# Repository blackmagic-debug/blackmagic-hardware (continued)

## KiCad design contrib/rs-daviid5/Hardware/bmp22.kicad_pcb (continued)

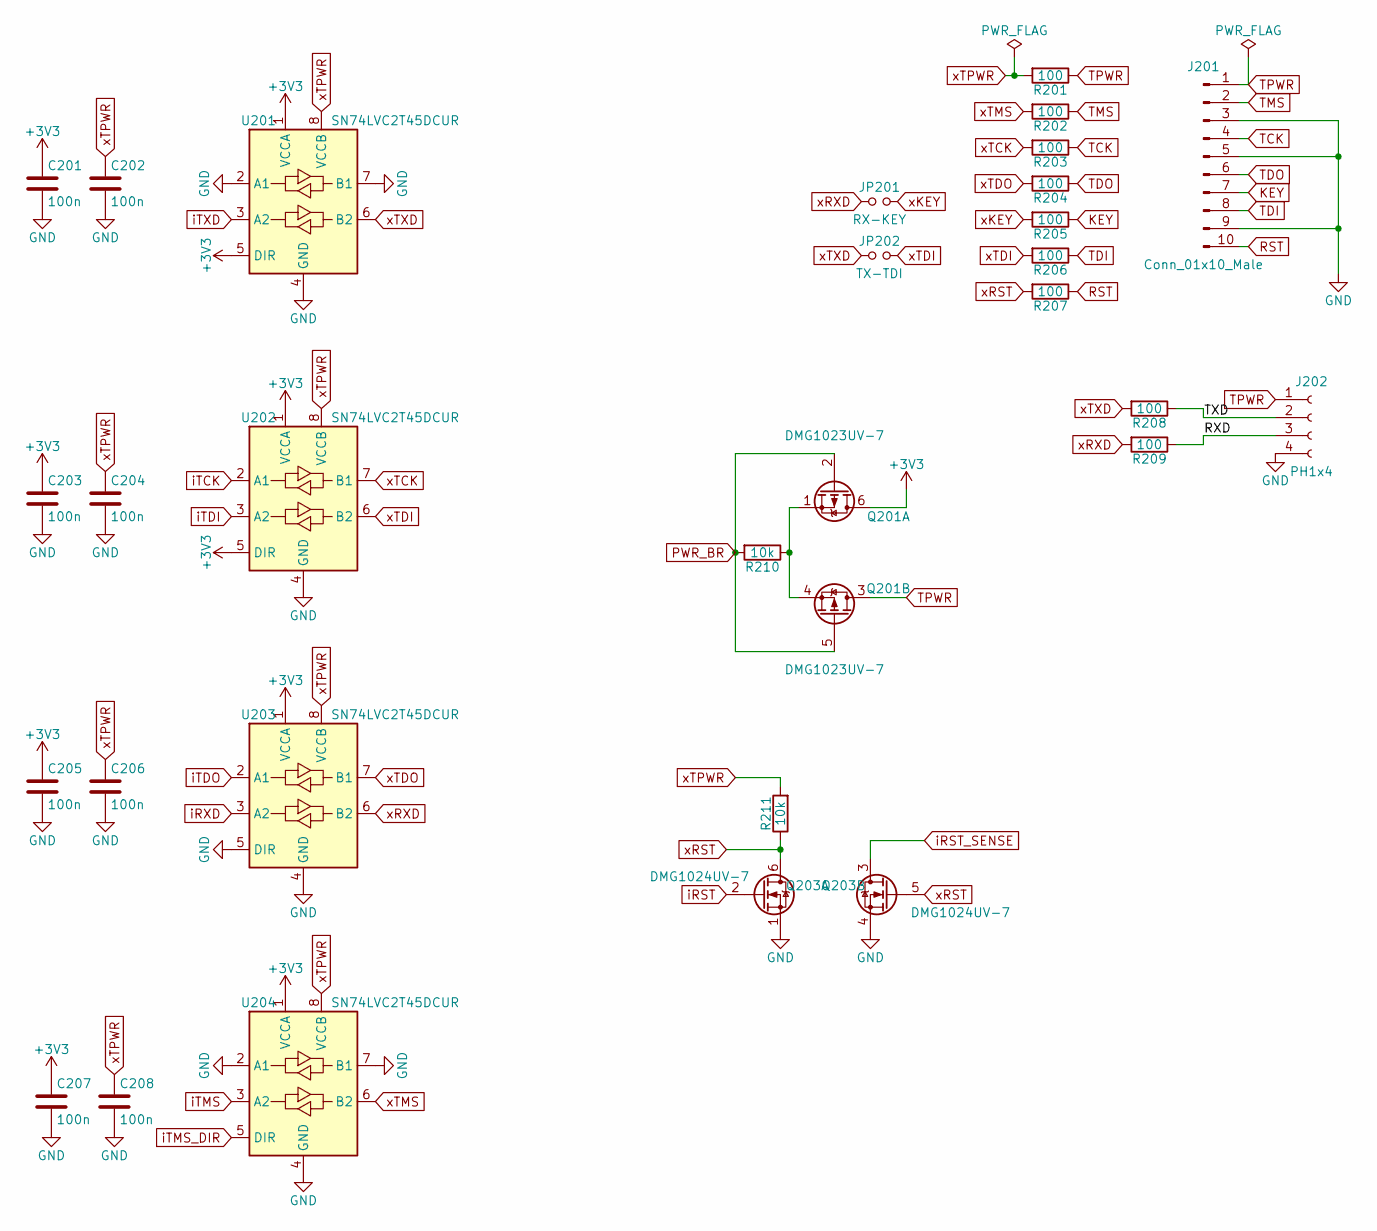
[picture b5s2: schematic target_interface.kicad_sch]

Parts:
C201, C202, C203, C204, C205, C206, C207, C208: 100n; C_0402_1005Metric; LCSC Number Part C14663
J201: Conn_01x10_Male; PinHeader_2x05_P1.27mm_Vertical_SMD; LCSC Number Part C150517
J202: PH1x4; JST_PH_S4B-PH-SM4-TB_1x04-1MP_P2.00mm_Horizontal; LCSC Number Part C265102
JP201: RX-KEY; R_0402_1005Metric; LCSC Number Part C60485
JP202: TX-TDI; R_0402_1005Metric; LCSC Number Part C60485
Q201: DMG1023UV-7; LCSC Number Part C212298
Q203: DMG1024UV-7; DMG1023UV-7; LCSC Number Part C212298
R201, R202, R203, R204, R205, R206, R207, R208, R209: 100; R_0402_1005Metric; LCSC Number Part C25076
R210, R211: 10k; R_0402_1005Metric; LCSC Number Part C25744
U201, U202, U203, U204: SN74LVC2T45DCUR; VSSOP-8_2.3x2mm_P0.5mm; LCSC Number Part C15741

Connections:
+3V3: C201.1, C203.1, C205.1, C207.1, Q201.6 (D), U201.1 (VCCA), U201.5 (DIR), U202.1 (VCCA), U202.5 (DIR), U203.1 (VCCA), U204.1 (VCCA); also elsewhere on the board
/Sheet5F21D67E/RXD: J202.3, R209.1
/Sheet5F21D67E/TXD: J202.2, R208.1
GND: C201.2, C202.2, C203.2, C204.2, C205.2, C206.2, C207.2, C208.2, J201.3, J201.5, J201.9, J202.4, Q203.1 (S), Q203.4 (S), U201.2 (A1), U201.4 (GND), U201.7 (B1), U202.4 (GND), U203.4 (GND), U203.5 (DIR), U204.2 (A1), U204.4 (GND), U204.7 (B1); also elsewhere on the board
KEY: J201.7, R205.1
unnamed: Q201.1 (S), Q201.4 (S), R210.1
PWR_BR: Q201.2 (G), Q201.5 (G), R210.2; also elsewhere on the board
RST: J201.10, R207.1
TCK: J201.4, R203.1
TDI: J201.8, R206.1
TDO: J201.6, R204.1
TMS: J201.2, R202.1
TPWR: J201.1, J202.1, Q201.3 (D), R201.1; also elsewhere on the board
iRST: Q203.2 (G); also elsewhere on the board
iRST_SENSE: Q203.3 (D); also elsewhere on the board
iRXD: U203.3 (A2); also elsewhere on the board
iTCK: U202.2 (A1); also elsewhere on the board
iTDI: U202.3 (A2); also elsewhere on the board
iTDO: U203.2 (A1); also elsewhere on the board
iTMS: U204.3 (A2); also elsewhere on the board
iTMS_DIR: U204.5 (DIR); also elsewhere on the board
iTXD: U201.3 (A2); also elsewhere on the board
xKEY: JP201.2, R205.2
xRST: Q203.5 (G), Q203.6 (D), R207.2, R211.1
xRXD: JP201.1, R209.2, U203.6 (B2)
xTCK: R203.2, U202.7 (B1)
xTDI: JP202.2, R206.2, U202.6 (B2)
xTDO: R204.2, U203.7 (B1)
xTMS: R202.2, U204.6 (B2)
xTPWR: C202.1, C204.1, C206.1, C208.1, R201.2, R211.2, U201.8 (VCCB), U202.8 (VCCB), U203.8 (VCCB), U204.8 (VCCB)
xTXD: JP202.1, R208.2, U201.6 (B2)

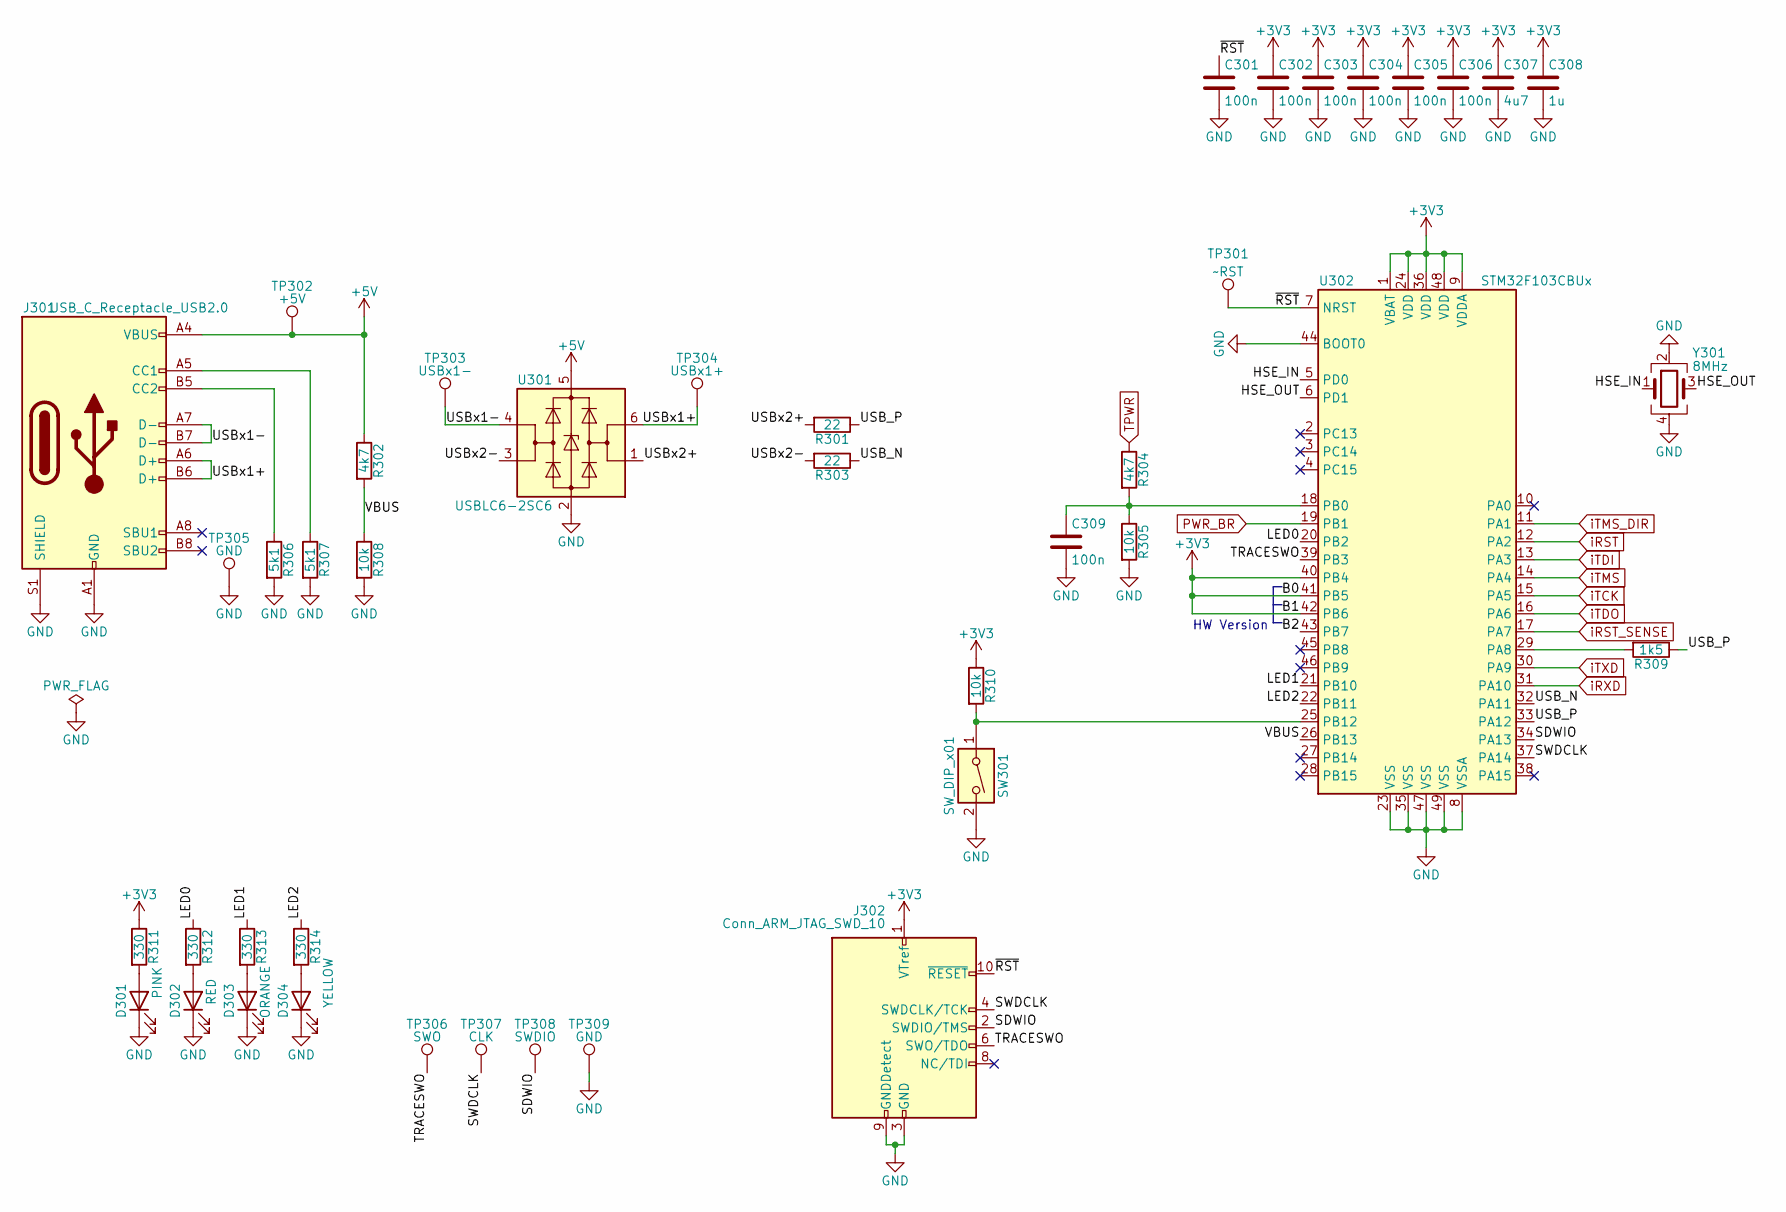
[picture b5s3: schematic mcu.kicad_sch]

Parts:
C301, C302, C303, C304, C305, C306, C309: 100n; C_0402_1005Metric; LCSC Number Part C14663
C307: 4u7; C_0603_1608Metric; LCSC Number Part C19666
C308: 1u; C_0603_1608Metric; LCSC Number Part C15849
D301: PINK; LED_1206_3216Metric; LCSC Number Part C268284
D302: RED; LED_0603_1608Metric; LCSC Number Part C375444
D303: ORANGE; LED_0603_1608Metric; LCSC Number Part C146215
D304: YELLOW; LED_0603_1608Metric; LCSC Number Part C89811
J301: USB_C_Receptacle_USB2.0; USB_C_Receptacle_Palconn_UTC16-G; LCSC Number Part C2760486
J302: Conn_ARM_JTAG_SWD_10; Tag-Connect_TC2050-IDC-NL_2x05_P1.27mm_Vertical
R301, R303: 22; R_0402_1005Metric; LCSC Number Part C25092
R302, R304: 4k7; R_0402_1005Metric; LCSC Number Part C25900
R305, R308, R310: 10k; R_0402_1005Metric; LCSC Number Part C25744
R306, R307: 5k1; R_0402_1005Metric; LCSC Number Part C25905
R309: 1k5; R_0402_1005Metric; LCSC Number Part C25867
R311, R312, R313, R314: 330; R_0402_1005Metric; LCSC Number Part C25104
SW301: SW_DIP_x01; SW_SPST_PTS810; LCSC Number Part C116501
TP301: ~RST; TestPoint_Pad_D1.5mm
TP302: +5V; TestPoint_Pad_D1.5mm
TP303: USBx1-; TestPoint_Pad_D1.5mm
TP304: USBx1+; TestPoint_Pad_D1.5mm
TP305, TP309: GND; TestPoint_Pad_D1.5mm
TP306: SWO; TestPoint_Pad_D1.5mm
TP307: CLK; TestPoint_Pad_D1.5mm
TP308: SWDIO; TestPoint_Pad_D1.5mm
U301: USBLC6-2SC6; SOT-23-6; LCSC Number Part C2827654
U302: STM32F103CBUx; TQFP48; LCSC Number Part C8304
Y301: 8MHz; Crystal_SMD_3225-4Pin_3.2x2.5mm; LCSC Number Part C435184

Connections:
+3V3: C302.1, C303.1, C304.1, C305.1, C306.1, C307.1, C308.1, J302.1 (VTref), R310.1, R311.1, U302.1 (VBAT), U302.9 (VDDA), U302.24 (VDD), U302.36 (VDD), U302.40 (PB4), U302.41 (PB5), U302.42 (PB6), U302.48 (VDD); also elsewhere on the board
+5V: J301.A4 (VBUS), J301.A9 (VBUS), J301.B4 (VBUS), J301.B9 (VBUS), R302.1, TP302.1, U301.5 (VBUS); also elsewhere on the board
/Sheet5F25207C/B2: U302.43 (PB7)
/Sheet5F25207C/HSE_IN: U302.5 (PD0), Y301.1
/Sheet5F25207C/HSE_OUT: U302.6 (PD1), Y301.3
/Sheet5F25207C/LED0: R312.1, U302.20 (PB2)
/Sheet5F25207C/LED1: R313.1, U302.21 (PB10)
/Sheet5F25207C/LED2: R314.1, U302.22 (PB11)
/Sheet5F25207C/SDWIO: J302.2 (SWDIO/TMS), TP308.1, U302.34 (PA13)
/Sheet5F25207C/SWDCLK: J302.4 (SWDCLK/TCK), TP307.1, U302.37 (PA14)
/Sheet5F25207C/TRACESWO: J302.6 (SWO/TDO), TP306.1, U302.39 (PB3)
/Sheet5F25207C/USB_N: R303.1, U302.32 (PA11)
/Sheet5F25207C/USB_P: R301.1, R309.1, U302.33 (PA12)
/Sheet5F25207C/USBx1+: J301.A6 (D+), J301.B6 (D+), TP304.1, U301.6 (I/O1)
/Sheet5F25207C/USBx1-: J301.A7 (D-), J301.B7 (D-), TP303.1, U301.4 (I/O2)
/Sheet5F25207C/USBx2+: R301.2, U301.1 (I/O1)
/Sheet5F25207C/USBx2-: R303.2, U301.3 (I/O2)
/Sheet5F25207C/VBUS: R302.2, R308.1, U302.26 (PB13)
/Sheet5F25207C/~RST: C301.1, J302.10 (~RESET), TP301.1, U302.7 (NRST)
GND: C301.2, C302.2, C303.2, C304.2, C305.2, C306.2, C307.2, C308.2, C309.2, D301.1 (K), D302.1 (K), D303.1 (K), D304.1 (K), J301.A1 (GND), J301.A12 (GND), J301.B1 (GND), J301.B12 (GND), J301.S1 (SHIELD), J302.3 (GND), J302.5 (GND), J302.9 (GNDDetect), R305.2, R306.2, R307.2, R308.2, SW301.2, TP305.1, TP309.1, U301.2 (GND), U302.8 (VSSA), U302.23 (VSS), U302.35 (VSS), U302.44 (BOOT0), U302.47 (VSS), U302.49 (VSS), Y301.2, Y301.4; also elsewhere on the board
unnamed: C309.1, R304.2, R305.1, U302.18 (PB0)
unnamed: D301.2 (A), R311.2
unnamed: D302.2 (A), R312.2
unnamed: D303.2 (A), R313.2
unnamed: D304.2 (A), R314.2
unnamed: J301.A5 (CC1), R307.1
unnamed: J301.B5 (CC2), R306.1
unnamed: R309.2, U302.29 (PA8)
unnamed: R310.2, SW301.1, U302.25 (PB12)
PWR_BR: U302.19 (PB1); also elsewhere on the board
TPWR: R304.1; also elsewhere on the board
iRST: U302.12 (PA2); also elsewhere on the board
iRST_SENSE: U302.17 (PA7); also elsewhere on the board
iRXD: U302.31 (PA10); also elsewhere on the board
iTCK: U302.15 (PA5); also elsewhere on the board
iTDI: U302.13 (PA3); also elsewhere on the board
iTDO: U302.16 (PA6); also elsewhere on the board
iTMS: U302.14 (PA4); also elsewhere on the board
iTMS_DIR: U302.11 (PA1); also elsewhere on the board
iTXD: U302.30 (PA9); also elsewhere on the board

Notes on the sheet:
HW Version

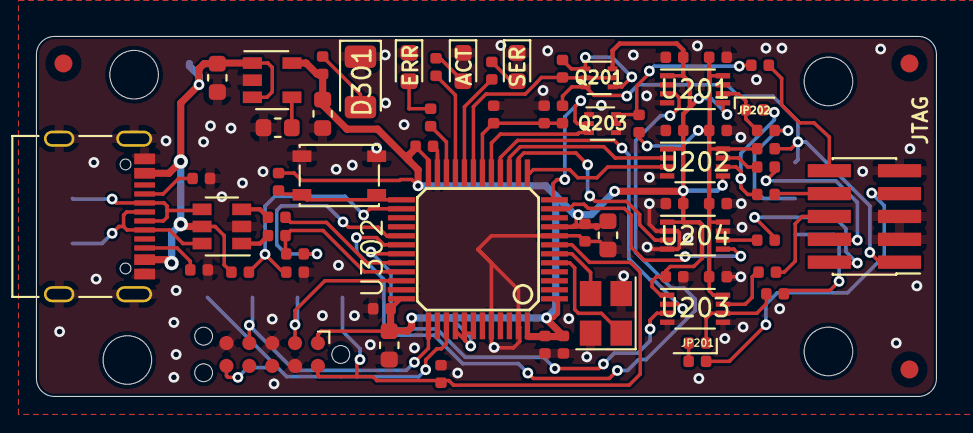
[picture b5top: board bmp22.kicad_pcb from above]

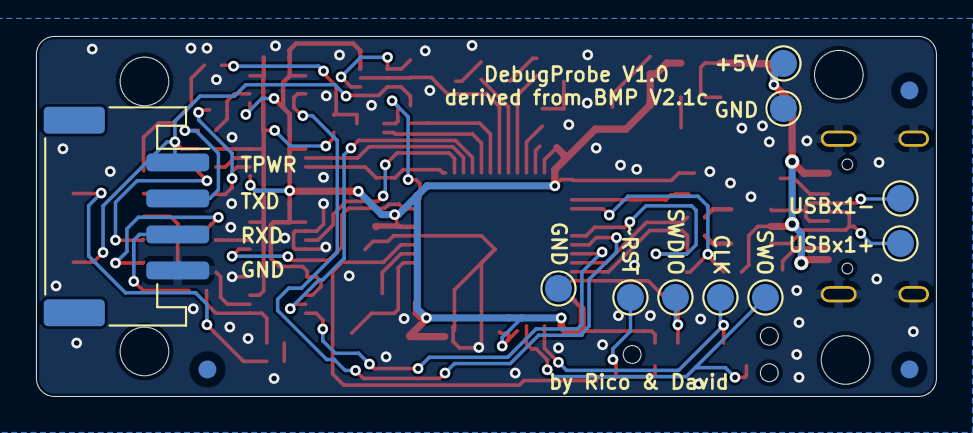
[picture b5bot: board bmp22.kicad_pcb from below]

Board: 2 copper layers, 50.0 x 20.0 mm, 85 parts (13 on the bottom side), 58 nets.

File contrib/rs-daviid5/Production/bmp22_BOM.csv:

"Source:","C:\Users\Sergio\Documents\EOS\bmp22\bmp22.kicad_sch"
"Date:","06/09/2022 16:51:32"
"Tool:","Eeschema (6.0.7)"
"Generator:","C:\Program Files\KiCad\6.0\bin\scripting\plugins/bom_csv_grouped_by_value.py"
"Component Count:","65"

"Individual Components:"

"Item","Qty","Reference(s)","Value","LibPart","Footprint","Datasheet","LCSC Number Part","Supplierlink"
"","","C101","1u","Device:C","Capacitor_SMD:C_0603_1608Metric","~","C15849",""
"","","C102","10n","Device:C","Capacitor_SMD:C_0603_1608Metric","~","C57112",""
"","","C103","1u","Device:C","Capacitor_SMD:C_0603_1608Metric","~","C15849",""
"","","C201","100n","Device:C","Capacitor_SMD:C_0402_1005Metric","~","C14663",""
"","","C202","100n","Device:C","Capacitor_SMD:C_0402_1005Metric","~","C14663",""
"","","C203","100n","Device:C","Capacitor_SMD:C_0402_1005Metric","~","C14663",""
"","","C204","100n","Device:C","Capacitor_SMD:C_0402_1005Metric","~","C14663",""
"","","C205","100n","Device:C","Capacitor_SMD:C_0402_1005Metric","~","C14663",""
"","","C206","100n","Device:C","Capacitor_SMD:C_0402_1005Metric","~","C14663",""
"","","C207","100n","Device:C","Capacitor_SMD:C_0402_1005Metric","~","C14663",""
"","","C208","100n","Device:C","Capacitor_SMD:C_0402_1005Metric","~","C14663",""
"","","C301","100n","Device:C","Capacitor_SMD:C_0402_1005Metric","~","C14663",""
"","","C302","100n","Device:C","Capacitor_SMD:C_0402_1005Metric","~","C14663",""
"","","C303","100n","Device:C","Capacitor_SMD:C_0402_1005Metric","~","C14663",""
"","","C304","100n","Device:C","Capacitor_SMD:C_0402_1005Metric","~","C14663",""
"","","C305","100n","Device:C","Capacitor_SMD:C_0402_1005Metric","~","C14663",""
"","","C306","100n","Device:C","Capacitor_SMD:C_0402_1005Metric","~","C14663",""
"","","C307","4u7","Device:C","Capacitor_SMD:C_0603_1608Metric","~","C19666",""
"","","C308","1u","Device:C","Capacitor_SMD:C_0603_1608Metric","~","C15849",""
"","","C309","100n","Device:C","Capacitor_SMD:C_0402_1005Metric","~","C14663",""
"","","D301","PINK","Device:LED","LED_SMD:LED_1206_3216Metric","~","C268284",""
"","","D302","RED","Device:LED","LED_SMD:LED_0603_1608Metric","~","C375444",""
"","","D303","ORANGE","Device:LED","LED_SMD:LED_0603_1608Metric","~","C146215",""
"","","D304","YELLOW","Device:LED","LED_SMD:LED_0603_1608Metric","~","C89811",""
"","","J201","Conn_01x10_Male","Connector:Conn_01x10_Male","Connector_PinHeader_1.27mm:PinHeader_2x05_P1.27mm_Vertical_SMD","~","C150517",""
"","","J202","PH1x4","Connector:Conn_01x04_Female","Connector_JST:JST_PH_S4B-PH-SM4-TB_1x04-1MP_P2.00mm_Horizontal","~","C265102",""
"","","J301","USB_C_Receptacle_USB2.0","bmp22-rescue:USB_C_Receptacle_USB2.0-Connector","Connector_USB:USB_C_Receptacle_Palconn_UTC16-G","https://www.usb.org/sites/default/files/documents/usb_type-c.zip","C2760486",""
"","","JP201","RX-KEY","bmp22-rescue:Jumper_NO_Small-Device","Resistor_SMD:R_0402_1005Metric","","C60485",""
"","","JP202","TX-TDI","bmp22-rescue:Jumper_NO_Small-Device","Resistor_SMD:R_0402_1005Metric","","C60485",""
"","","Q201","DMG1023UV-7","bmp22-rescue:Q_DUAL_PMOS_S1G1D2S2G2D1-Device","EOS:DMG1023UV-7","","C212298",""
"","","Q203","DMG1024UV-7","bmp22-rescue:Q_DUAL_NMOS_S1G1D2S2G2D1-Device","EOS:DMG1023UV-7","","C212298",""
"","","R201","100","Device:R","Resistor_SMD:R_0402_1005Metric","~","C25076",""
"","","R202","100","Device:R","Resistor_SMD:R_0402_1005Metric","~","C25076",""
"","","R203","100","Device:R","Resistor_SMD:R_0402_1005Metric","~","C25076",""
"","","R204","100","Device:R","Resistor_SMD:R_0402_1005Metric","~","C25076",""
"","","R205","100","Device:R","Resistor_SMD:R_0402_1005Metric","~","C25076",""
"","","R206","100","Device:R","Resistor_SMD:R_0402_1005Metric","~","C25076",""
"","","R207","100","Device:R","Resistor_SMD:R_0402_1005Metric","~","C25076",""
"","","R208","100","Device:R","Resistor_SMD:R_0402_1005Metric","~","C25076",""
"","","R209","100","Device:R","Resistor_SMD:R_0402_1005Metric","~","C25076",""
"","","R210","10k","Device:R","Resistor_SMD:R_0402_1005Metric","~","C25744",""
"","","R211","10k","Device:R","Resistor_SMD:R_0402_1005Metric","~","C25744",""
"","","R301","22","Device:R","Resistor_SMD:R_0402_1005Metric","~","C25092",""
"","","R302","4k7","Device:R","Resistor_SMD:R_0402_1005Metric","~","C25900",""
"","","R303","22","Device:R","Resistor_SMD:R_0402_1005Metric","~","C25092",""
"","","R304","4k7","Device:R","Resistor_SMD:R_0402_1005Metric","~","C25900",""
"","","R305","10k","Device:R","Resistor_SMD:R_0402_1005Metric","~","C25744",""
"","","R306","5k1","Device:R","Resistor_SMD:R_0402_1005Metric","~","C25905",""
"","","R307","5k1","Device:R","Resistor_SMD:R_0402_1005Metric","~","C25905",""
"","","R308","10k","Device:R","Resistor_SMD:R_0402_1005Metric","~","C25744",""
"","","R309","1k5","Device:R","Resistor_SMD:R_0402_1005Metric","~","C25867",""
"","","R310","10k","Device:R","Resistor_SMD:R_0402_1005Metric","~","C25744",""
"","","R311","330","Device:R","Resistor_SMD:R_0402_1005Metric","~","C25104",""
"","","R312","330","Device:R","Resistor_SMD:R_0402_1005Metric","~","C25104",""
"","","R313","330","Device:R","Resistor_SMD:R_0402_1005Metric","~","C25104",""
"","","R314","330","Device:R","Resistor_SMD:R_0402_1005Metric","~","C25104",""
"","","SW301","SW_DIP_x01","Switch:SW_DIP_x01","Button_Switch_SMD:SW_SPST_PTS810","~","C116501",""
"","","U101","LP2985-3.3","Regulator_Linear:LP2985-3.3","Package_TO_SOT_SMD:SOT-23-5","http://www.ti.com/lit/ds/symlink/lp2985.pdf","C95414",""
"","","U201","SN74LVC2T45DCUR","Logic_LevelTranslator:SN74LVC2T45DCUR","Package_SO:VSSOP-8_2.3x2mm_P0.5mm","http://www.ti.com/lit/ds/symlink/sn74lvc2t45.pdf","C15741",""
"","","U202","SN74LVC2T45DCUR","Logic_LevelTranslator:SN74LVC2T45DCUR","Package_SO:VSSOP-8_2.3x2mm_P0.5mm","http://www.ti.com/lit/ds/symlink/sn74lvc2t45.pdf","C15741",""
"","","U203","SN74LVC2T45DCUR","Logic_LevelTranslator:SN74LVC2T45DCUR","Package_SO:VSSOP-8_2.3x2mm_P0.5mm","http://www.ti.com/lit/ds/symlink/sn74lvc2t45.pdf","C15741",""
"","","U204","SN74LVC2T45DCUR","Logic_LevelTranslator:SN74LVC2T45DCUR","Package_SO:VSSOP-8_2.3x2mm_P0.5mm","http://www.ti.com/lit/ds/symlink/sn74lvc2t45.pdf","C15741",""
"","","U301","USBLC6-2SC6","Power_Protection:USBLC6-2SC6","Package_TO_SOT_SMD:SOT-23-6","https://www.st.com/resource/en/datasheet/usblc6-2.pdf","C2827654",""
"","","U302","STM32F103CBUx","MCU_ST_STM32F1:STM32F103CBUx","Package_DFN_QFN:QFN-48-1EP_7x7mm_P0.5mm_EP5.6x5.6mm","http://www.st.com/st-web-ui/static/active/en/resource/techni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","C8304",""
"","","Y301","8MHz","Device:Crystal_GND24","Crystal:Crystal_SMD_3225-4Pin_3.2x2.5mm","~","C435184","https://www.digikey.de/product-detail/de/ecs-inc/ECS-80-12-3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"

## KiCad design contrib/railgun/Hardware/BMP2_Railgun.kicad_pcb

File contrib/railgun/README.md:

Black Magic Railgun Clone
========================================

Railgun is a version of the Black Magic Mini board. Unlike other Black Magic boards it contains a USB-A connector instead of a type C one.

It is an easy-to-use board used for debugging embedded microcontrollers. It supports several targets from manufacturers such as STMicroelectronics, Atmel, Nordic Semiconductor, NXP, Texas Instruments, Freescale, Silicon Labs, Xilinx or Raspberry Pi.

GNU debugger
-------------------
The Black Magic GNU DeBugger (GDB) server features:
* Automatic target detection
* No need for target specific configuration scripts
* Easily scriptable
* Interface to the host computer does not require special drivers
* Full debugging functionality
* Works with Windows, Linux and Mac environments

Repository Contents
-------------------

* **/Production** - Gerber files, drill files, BOM, CPL file
* **/Hardware** - KiCad PCB files, footprints library
* **/Documents** - Schematics pdf

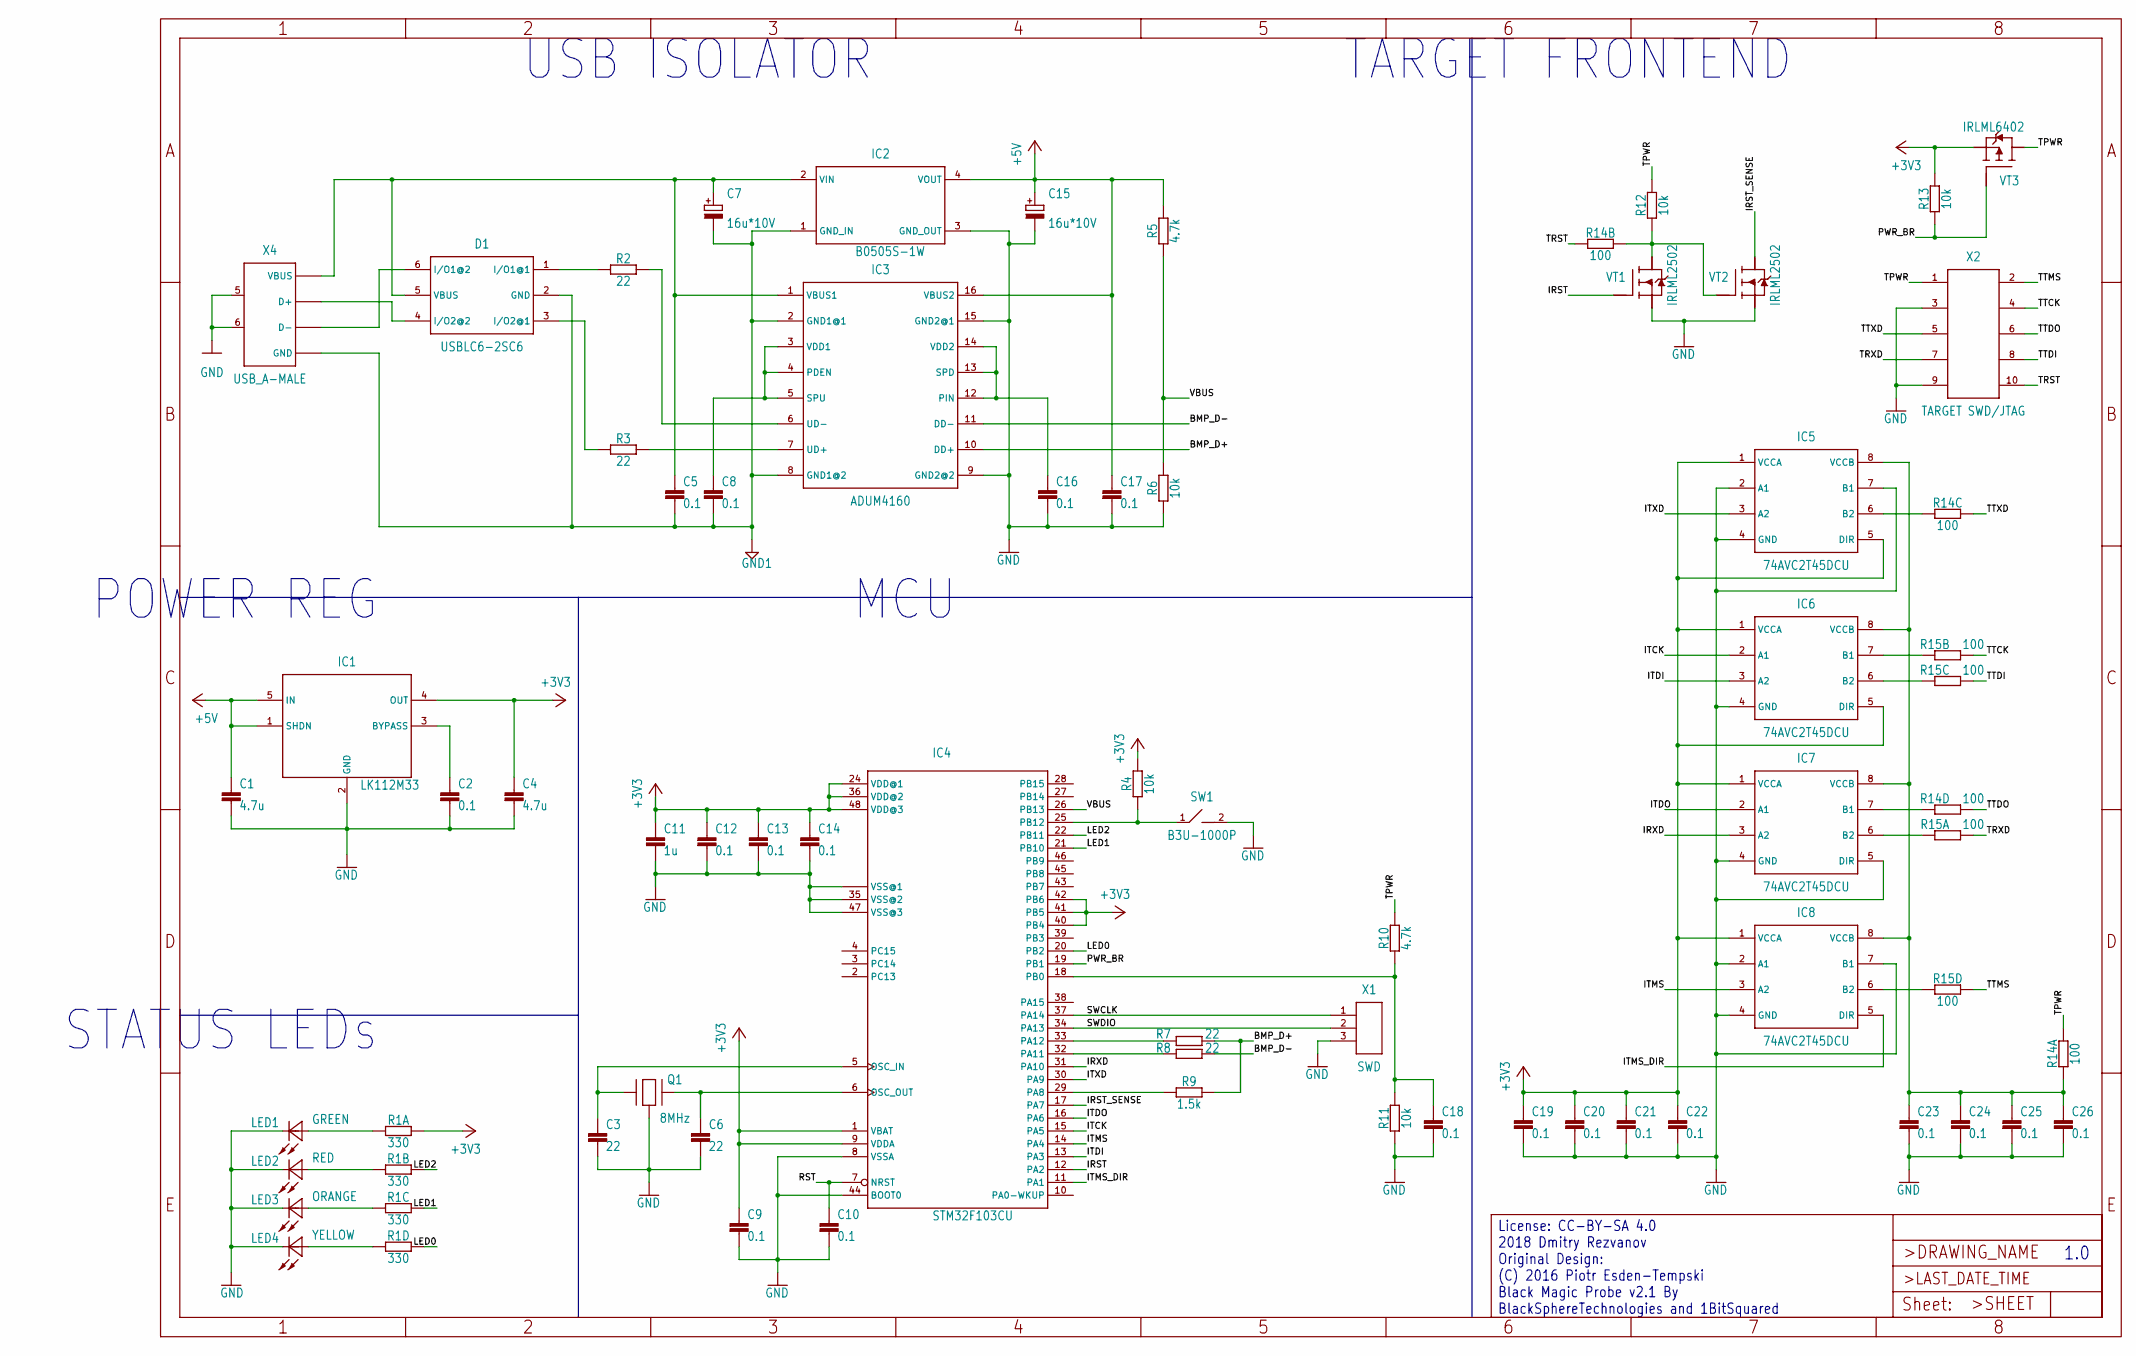
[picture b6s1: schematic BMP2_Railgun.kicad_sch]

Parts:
C1, C4: 4.7u; 0603; LCSC Number Part C8032
C2, C5, C8, C9, C10, C12, C13, C14, C16, C17, C18, C19, C20, C21, C22, C23, C24, C25, C26: 0.1; 0402; LCSC Number Part C83056
C3, C6: 22; 0402; LCSC Number Part C1555
C7, C15: 16u*10V; C3216_A; LCSC Number Part C30330
C11: 1u; 0603; LCSC Number Part C1592
D1: USBLC6-2SC6; SOT23-6L; LCSC Number Part C2827654
IC1: LK112M33; SOT23-5L; LCSC Number Part C155584
IC2: B0505S-1W; 4SIP; LCSC Number Part C2912568
IC3: ADUM4160; SO-16W; LCSC Number Part C57791
IC4: STM32F103CU; TQFP48; LCSC Number Part C8734
IC5, IC6, IC7, IC8: 74AVC2T45DCU; S-PDSO-G8; LCSC Number Part C140318
LED1: GREEN; LED0603; LCSC Number Part C434420
LED2: RED; LED0603; LCSC Number Part C375444
LED3: ORANGE; LED0603; LCSC Number Part C146215
LED4: YELLOW; LED0603; LCSC Number Part C89811
Q1: 8MHz; 3225; LCSC Number Part C403948
R1: 330; ARRAY_0603; LCSC Number Part C12018
R2, R3, R7, R8: 22; 0402; LCSC Number Part C25152
R4, R6, R11, R12, R13: 10k; 0402; LCSC Number Part C140214
R5, R10: 4.7k; 0402; LCSC Number Part C304616
R9: 1.5k; 0402; LCSC Number Part C286554
R14, R15: 100; ARRAY_0603; LCSC Number Part C79203
SW1: B3U-1000P; LCSC Number Part C231329
VT1, VT2: IRLML2502; SOT23; LCSC Number Part C518800
VT3: IRLML6402; SOT23; LCSC Number Part C347504
X1: SWD; PH1X03_1.27
X2: TARGET SWD/JTAG; IDC-10(FACE)
X4: USB_A-MALE; USB-A-TH_48037-0001; LCSC Number Part C112454

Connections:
+3V3: C4.1, C9.1, C11.1, C12.1, C13.1, C14.1, C19.1, C20.1, C21.1, C22.1, IC1.4 (OUT), IC4.1 (VBAT), IC4.9 (VDDA), IC4.24 (VDD@1), IC4.36 (VDD@2), IC4.40 (PB4), IC4.41 (PB5), IC4.42 (PB6), IC4.48 (VDD@3), IC5.1 (VCCA), IC5.5 (DIR), IC6.1 (VCCA), IC6.5 (DIR), IC7.1 (VCCA), IC8.1 (VCCA), R1.1, R4.1, R13.1, VT3.2 (S)
+5V: C1.1, C15.2 (+), C17.1, IC1.1 (SHDN), IC1.5 (IN), IC2.4 (VOUT), IC3.16 (VBUS2), R5.1
/BMP_D+: IC3.10 (DD+), R7.1, R9.1
/BMP_D-: IC3.11 (DD-), R8.1
/IRST: IC4.12 (PA2), VT1.1 (G)
/IRST_SENSE: IC4.17 (PA7), VT2.3 (D)
/IRXD: IC4.31 (PA10), IC7.3 (A2)
/ITCK: IC4.15 (PA5), IC6.2 (A1)
/ITDI: IC4.13 (PA3), IC6.3 (A2)
/ITDO: IC4.16 (PA6), IC7.2 (A1)
/ITMS: IC4.14 (PA4), IC8.3 (A2)
/ITMS_DIR: IC4.11 (PA1), IC8.5 (DIR)
/ITXD: IC4.30 (PA9), IC5.3 (A2)
/LED0: IC4.20 (PB2), R1.4 (1)
/LED1: IC4.21 (PB10), R1.3 (1)
/LED2: IC4.22 (PB11), R1.2 (1)
/PWR_BR: IC4.19 (PB1), R13.2, VT3.1 (G)
/RST: C10.1, IC4.7 (NRST)
/SWCLK: IC4.37 (PA14), X1.1
/SWDIO: IC4.34 (PA13), X1.2
/TPWR: R10.1, R12.2, R14.8 (2), VT3.3 (D), X2.1
/TRST: R14.7 (2), X2.10
/TRXD: R15.8 (2), X2.7
/TTCK: R15.7 (2), X2.4
/TTDI: R15.6 (2), X2.8
/TTDO: R14.5 (2), X2.6
/TTMS: R15.5 (2), X2.2
/TTXD: R14.6 (2), X2.5
/VBUS: IC4.26 (PB13), R5.2, R6.1
GND: C1.2, C2.2, C3.2, C4.2, C6.2, C9.2, C10.2, C11.2, C12.2, C13.2, C14.2, C15.1 (-), C16.2, C17.2, C18.2, C19.2, C20.2, C21.2, C22.2, C23.2, C24.2, C25.2, C26.2, IC1.2 (GND), IC2.3 (GND_OUT), IC3.9 (GND2@2), IC3.15 (GND2@1), IC4.8 (VSSA), IC4.23 (VSS@1), IC4.35 (VSS@2), IC4.44 (BOOT0), IC4.47 (VSS@3), IC4.49 (VSS@1), IC5.2 (A1), IC5.4 (GND), IC5.7 (B1), IC6.4 (GND), IC7.4 (GND), IC7.5 (DIR), IC8.2 (A1), IC8.4 (GND), IC8.7 (B1), LED1.2 (C), LED2.2 (C), LED3.2 (C), LED4.2 (C), Q1.2 (GND), Q1.4 (GND), R6.2, R11.2, SW1.2, VT1.2 (S), VT2.2 (S), X1.3, X2.3, X2.9, X4.5, X4.6
GND1: C5.2, C7.1 (-), C8.2, D1.2 (GND), IC2.1 (GND_IN), IC3.2 (GND1@1), IC3.8 (GND1@2), X4.1 (GND), X4.GND@1 (GND), X4.GND@2 (GND)
unnamed: C2.1, IC1.3 (BYPASS)
unnamed: C3.1, IC4.5 (OSC_IN), Q1.1
unnamed: C5.1, C7.2 (+), D1.5 (VBUS), IC2.2 (VIN), IC3.1 (VBUS1), X4.4 (VBUS)
unnamed: C6.1, IC4.6 (OSC_OUT), Q1.3 (2)
unnamed: C8.1, IC3.3 (VDD1), IC3.4 (PDEN), IC3.5 (SPU)
unnamed: C16.1, IC3.12 (PIN), IC3.13 (SPD), IC3.14 (VDD2)
unnamed: C18.1, IC4.18 (PB0), R10.2, R11.1
unnamed: C23.1, C24.1, C25.1, C26.1, IC5.8 (VCCB), IC6.8 (VCCB), IC7.8 (VCCB), IC8.8 (VCCB), R14.1
unnamed: D1.1 (I/O1@1), R2.1
unnamed: D1.3 (I/O2@1), R3.1
unnamed: D1.4 (I/O2@2), X4.2 (D+)
unnamed: D1.6 (I/O1@2), X4.3 (D-)
unnamed: IC3.6 (UD-), R2.2
unnamed: IC3.7 (UD+), R3.2
unnamed: IC4.25 (PB12), R4.2, SW1.1
unnamed: IC4.29 (PA8), R9.2
unnamed: IC4.32 (PA11), R8.2
unnamed: IC4.33 (PA12), R7.2
unnamed: IC5.6 (B2), R14.3 (1)
unnamed: IC6.6 (B2), R15.3 (1)
unnamed: IC6.7 (B1), R15.2 (1)
unnamed: IC7.6 (B2), R15.1
unnamed: IC7.7 (B1), R14.4 (1)
unnamed: IC8.6 (B2), R15.4 (1)
unnamed: LED1.1 (A), R1.8 (2)
unnamed: LED2.1 (A), R1.7 (2)
unnamed: LED3.1 (A), R1.6 (2)
unnamed: LED4.1 (A), R1.5 (2)
unnamed: R12.1, R14.2 (1), VT1.3 (D), VT2.1 (G)

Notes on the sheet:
1.0
USB ISOLATOR
TARGET FRONTEND
STATUS LEDs
POWER REG
MCU
License: CC-BY-SA 4.0 2018 Dmitry Rezvanov Original Design: (C) 2016 Piotr Esden-Tempski Black Magic Probe v2.1 By BlackSphereTechnologies and 1BitSquared

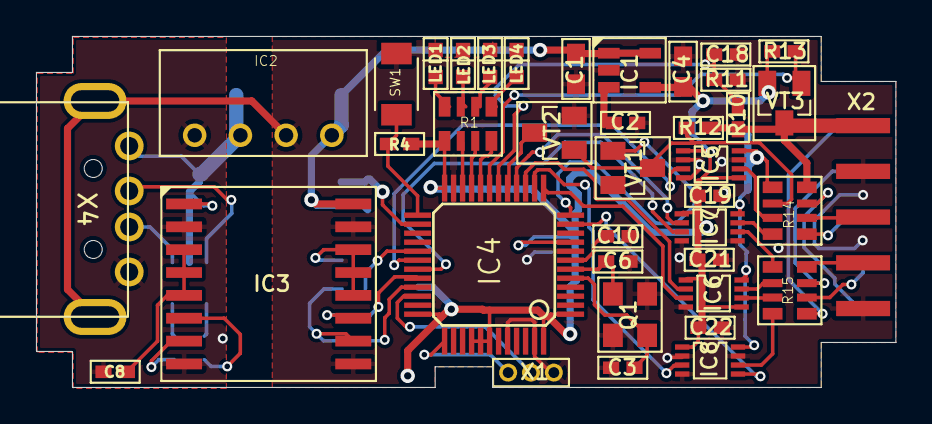
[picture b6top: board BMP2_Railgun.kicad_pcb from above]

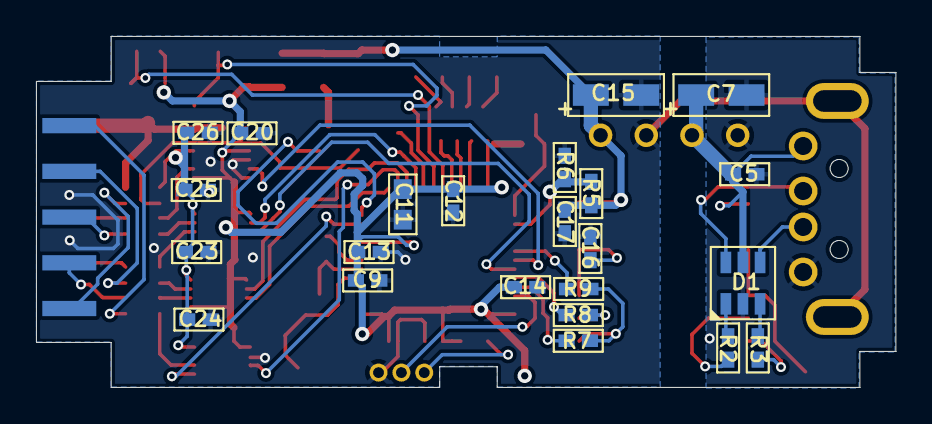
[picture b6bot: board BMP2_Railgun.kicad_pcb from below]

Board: 2 copper layers, 47.8 x 19.5 mm, 62 parts (23 on the bottom side), 60 nets.

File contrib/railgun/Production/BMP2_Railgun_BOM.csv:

"Source:","C:\Users\Sergio\Documents\EOS\railgun\railgun_KiCAD\BMP2_Railgun.kicad_sch"
"Date:","07/09/2022 18:05:11"
"Tool:","Eeschema (6.0.7)"
"Generator:","C:\Program Files\KiCad\6.0\bin\scripting\plugins/bom_csv_grouped_by_value.py"
"Component Count:","60"

"Individual Components:"

"Item","Qty","Reference(s)","Value","LibPart","Footprint","Datasheet","LCSC Number Part"
"","","C1","4.7u","BMP2_Railgun-eagle-import:C_0603","BMP2_Railgun:0603","","C8032"
"","","C2","0.1","BMP2_Railgun-eagle-import:C_0402","BMP2_Railgun:0402","","C83056"
"","","C3","22","BMP2_Railgun-eagle-import:C_0402","BMP2_Railgun:0402","","C1555"
"","","C4","4.7u","BMP2_Railgun-eagle-import:C_0603","BMP2_Railgun:0603","","C8032"
"","","C5","0.1","BMP2_Railgun-eagle-import:C_0603","BMP2_Railgun:0402","","C83056"
"","","C6","22","BMP2_Railgun-eagle-import:C_0402","BMP2_Railgun:0402","","C1555"
"","","C7","16u*10V","BMP2_Railgun-eagle-import:C_POL_3216{slash}A","BMP2_Railgun:C3216_A","","C30330"
"","","C8","0.1","BMP2_Railgun-eagle-import:C_0402","BMP2_Railgun:0402","","C83056"
"","","C9","0.1","BMP2_Railgun-eagle-import:C_0402","BMP2_Railgun:0402","","C83056"
"","","C10","0.1","BMP2_Railgun-eagle-import:C_0402","BMP2_Railgun:0402","","C83056"
"","","C11","1u","BMP2_Railgun-eagle-import:C_0603","BMP2_Railgun:0603","","C1592"
"","","C12","0.1","BMP2_Railgun-eagle-import:C_0402","BMP2_Railgun:0402","","C83056"
"","","C13","0.1","BMP2_Railgun-eagle-import:C_0402","BMP2_Railgun:0402","","C83056"
"","","C14","0.1","BMP2_Railgun-eagle-import:C_0402","BMP2_Railgun:0402","","C83056"
"","","C15","16u*10V","BMP2_Railgun-eagle-import:C_POL_3216{slash}A","BMP2_Railgun:C3216_A","","C30330"
"","","C16","0.1","BMP2_Railgun-eagle-import:C_0402","BMP2_Railgun:0402","","C83056"
"","","C17","0.1","BMP2_Railgun-eagle-import:C_0603","BMP2_Railgun:0402","","C83056"
"","","C18","0.1","BMP2_Railgun-eagle-import:C_0402","BMP2_Railgun:0402","","C83056"
"","","C19","0.1","BMP2_Railgun-eagle-import:C_0402","BMP2_Railgun:0402","","C83056"
"","","C20","0.1","BMP2_Railgun-eagle-import:C_0402","BMP2_Railgun:0402","","C83056"
"","","C21","0.1","BMP2_Railgun-eagle-import:C_0402","BMP2_Railgun:0402","","C83056"
"","","C22","0.1","BMP2_Railgun-eagle-import:C_0402","BMP2_Railgun:0402","","C83056"
"","","C23","0.1","BMP2_Railgun-eagle-import:C_0402","BMP2_Railgun:0402","","C83056"
"","","C24","0.1","BMP2_Railgun-eagle-import:C_0402","BMP2_Railgun:0402","","C83056"
"","","C25","0.1","BMP2_Railgun-eagle-import:C_0402","BMP2_Railgun:0402","","C83056"
"","","C26","0.1","BMP2_Railgun-eagle-import:C_0402","BMP2_Railgun:0402","","C83056"
"","","D1","USBLC6-2SC6","BMP2_Railgun-eagle-import:USBLC6-2SC6","BMP2_Railgun:SOT23-6L","","C2827654"
"","","IC1","LK112M33","BMP2_Railgun-eagle-import:LK112M33","BMP2_Railgun:SOT23-5L","","C155584"
"","","IC2","B0505S-1W","BMP2_Railgun-eagle-import:B0505S-1W","BMP2_Railgun:4SIP","","C2912568"
"","","IC3","ADUM4160","BMP2_Railgun-eagle-import:ADUM4160","BMP2_Railgun:SO-16W","","C57791"
"","","IC4","STM32F103CU","BMP2_Railgun-eagle-import:STM32F103CU","bmp_entropia:TQFP48","","C8734"
"","","IC5","74AVC2T45DCU","BMP2_Railgun-eagle-import:74AVC2T45DCU","BMP2_Railgun:S-PDSO-G8","","C140318"
"","","IC6","74AVC2T45DCU","BMP2_Railgun-eagle-import:74AVC2T45DCU","BMP2_Railgun:S-PDSO-G8","","C140318"
"","","IC7","74AVC2T45DCU","BMP2_Railgun-eagle-import:74AVC2T45DCU","BMP2_Railgun:S-PDSO-G8","","C140318"
"","","IC8","74AVC2T45DCU","BMP2_Railgun-eagle-import:74AVC2T45DCU","BMP2_Railgun:S-PDSO-G8","","C140318"
"","","LED1","GREEN","BMP2_Railgun-eagle-import:SMD_LED_0603","BMP2_Railgun:LED0603","","C434420"
"","","LED2","RED","BMP2_Railgun-eagle-import:SMD_LED_0603","BMP2_Railgun:LED0603","","C375444"
"","","LED3","ORANGE","BMP2_Railgun-eagle-import:SMD_LED_0603","BMP2_Railgun:LED0603","","C146215"
"","","LED4","YELLOW","BMP2_Railgun-eagle-import:SMD_LED_0603","BMP2_Railgun:LED0603","","C89811"
"","","Q1","8MHz","BMP2_Railgun-eagle-import:SMD_3225","BMP2_Railgun:3225","","C403948"
"","","R1","330","BMP2_Railgun-eagle-import:R_ARRAY_4X0603","BMP2_Railgun:ARRAY_0603","","C12018"
"","","R2","22","BMP2_Railgun-eagle-import:R_0402","BMP2_Railgun:0402","","C25152"
"","","R3","22","BMP2_Railgun-eagle-import:R_0402","BMP2_Railgun:0402","","C25152"
"","","R4","10k","BMP2_Railgun-eagle-import:R_0402","BMP2_Railgun:0402","","C140214"
"","","R5","4.7k","BMP2_Railgun-eagle-import:R_0402","BMP2_Railgun:0402","","C304616"
"","","R6","10k","BMP2_Railgun-eagle-import:R_0402","BMP2_Railgun:0402","","C140214"
"","","R7","22","BMP2_Railgun-eagle-import:R_0402","BMP2_Railgun:0402","","C25152"
"","","R8","22","BMP2_Railgun-eagle-import:R_0402","BMP2_Railgun:0402","","C25152"
"","","R9","1.5k","BMP2_Railgun-eagle-import:R_0402","BMP2_Railgun:0402","","C286554"
"","","R10","4.7k","BMP2_Railgun-eagle-import:R_0402","BMP2_Railgun:0402","","C304616"
"","","R11","10k","BMP2_Railgun-eagle-import:R_0402","BMP2_Railgun:0402","","C140214"
"","","R12","10k","BMP2_Railgun-eagle-import:R_0402","BMP2_Railgun:0402","","C140214"
"","","R13","10k","BMP2_Railgun-eagle-import:R_0402","BMP2_Railgun:0402","","C140214"
"","","R14","100","BMP2_Railgun-eagle-import:R_ARRAY_4X0603","BMP2_Railgun:ARRAY_0603","","C79203"
"","","R15","100","BMP2_Railgun-eagle-import:R_ARRAY_4X0603","BMP2_Railgun:ARRAY_0603","","C79203"
"","","SW1","B3U-1000P","BMP2_Railgun-eagle-import:B3U-1000P","BMP2_Railgun:B3U-1000P","","C231329"
"","","VT1","IRLML2502","BMP2_Railgun-eagle-import:IRLML2502","BMP2_Railgun:SOT23","","C518800"
"","","VT2","IRLML2502","BMP2_Railgun-eagle-import:IRLML2502","BMP2_Railgun:SOT23","","C518800"
"","","VT3","IRLML6402","BMP2_Railgun-eagle-import:IRLML6402","BMP2_Railgun:SOT23","","C347504"
"","","X4","USB_A-MALE","BMP2_Railgun-eagle-import:USB_A-MALE","BMP2_Railgun:USB-A-TH_48037-0001","","C112454"
